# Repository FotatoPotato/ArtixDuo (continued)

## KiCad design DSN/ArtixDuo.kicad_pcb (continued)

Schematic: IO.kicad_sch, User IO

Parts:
C38, C39, C40, C41, C51, C52, C54, C166, C167, C168, C169, C170: 100nF; C_0402_1005Metric; MFR PN GRM155R71E104KE14J
C53, C163, C164, C165, C171, C172, C187, C188, C189, C190: 100nF; C_0402_1005Metric; MFR PN GRM155R71H104ME14J
C177, C197: 1nF; C_0402_1005Metric
C178, C179, C185, C186, C194, C196: 10uF; C_0805_2012Metric; MFR PN GRM21BC71E106KE01K
D12, D13, D14, D15, D16, D17, D18, D19, D20, D21, D22, D23, D24, D25, D26, D27: LED GREEN; LED_0603_1608Metric; MFR PN 150060VS75000
F1, F2: Fuse; Fuse_0603_1608Metric
J6, J8, J9: Conn_02x40_Top_Bottom; PinSocket_2x40_P2.54mm_Vertical
J7, J10: 47272-0001; MOLEX_47272-0001; MFR PN 47272-0001
J11, J12, J13, J14, J15, J16, J17, J18, J19: 5-1814832-1; RF_SMA_Vertical_5-1814832-1; MPN 5-1814832-1; Digi-Key_PN A97594-ND
J20, J21, J22, J23, J24, J25, J26, J33: Conn_02x06_Odd_Even; PinHeader_2x06_P2.54mm_Horizontal
Q5, Q6, Q7, Q8, Q9, Q10, Q11, Q12, Q13, Q14, Q15, Q16, Q17, Q18, Q19, Q20: 2N7002; SOT-23-3; MPN 2N7002; Digi-Key_PN 2N7002NCT-ND
R26, R27, R72, R73, R78, R79, R80, R104: 1Meg; R_0402_1005Metric
R28, R69, R71, R81: 100K; R_0402_1005Metric; MFR PN RT0402FRE07100KL
R65, R66, R67, R68, R88, R89, R90, R91, R111, R112, R113, R114, R115, R116, R117, R118, R124, R125, R126, R127, R128, R129, R130, R131, R136, R137, R138, R139, R140, R141, R142, R143, R144, R145, R146, R147, R148, R149, R150, R151: 3K3; R_0402_1005Metric; MFR PN RC0402FR-073K3L
R70: 1K; R_0402_1005Metric
R74, R75, R76, R77, R96, R97, R98, R99: 100K; R_0402_1005Metric; MFR PN RC0402FR-07100KL
R82, R119, R120, R121, R122, R123, R132, R133, R134, R135, R212, R213, R214, R215, R216, R226, R227, R228, R229: 0R; R_0402_1005Metric
R207, R208, R209, R210, R211, R217, R218, R219, R220, R221, R222, R223, R224, R225, R230, R231, R232, R233: DNF; R_0402_1005Metric
SW10, SW11, SW12, SW13, SW18, SW19, SW20, SW21: SW_Push; SW_SPST_EVQQ2

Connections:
+3V3: C178.1, C185.1, C194.1, F1.2, F2.2, J6.1, J6.2, J6.41, J6.42, J8.1, J8.2, J8.41, J8.42, J9.1, J9.2, J9.41, J9.42, J20.1, J20.2, J21.1, J21.2, J22.1, J22.2, J23.1, J23.2, J24.1, J24.2, J25.1, J25.2, J26.1, J26.2, J33.1, J33.2, R28.1, R65.1, R66.1, R67.1, R68.1, R79.2, R88.1, R89.1, R90.1, R91.1, R113.1, R114.1, R117.1, R118.1, R126.1, R127.1, R130.1, R131.1, R138.1, R139.1, R142.1, R143.1, R146.1, R147.1, R150.1, R151.1; also elsewhere on the board
/TopSheet/FPGA_0/FPGA_0_GTP_CLK1_N: R216.2, R221.1; also elsewhere on the board
/TopSheet/FPGA_0/FPGA_0_GTP_CLK1_P: R123.2, R221.2; also elsewhere on the board
/TopSheet/FPGA_0/FPGA_0_LED0: Q13.1 (G), R136.1; also elsewhere on the board
/TopSheet/FPGA_0/FPGA_0_LED1: Q15.1 (G), R140.1; also elsewhere on the board
/TopSheet/FPGA_0/FPGA_0_LED2: Q17.1 (G), R144.1; also elsewhere on the board
/TopSheet/FPGA_0/FPGA_0_LED3: Q19.1 (G), R148.1; also elsewhere on the board
/TopSheet/FPGA_0/FPGA_0_LED4: Q14.1 (G), R137.1; also elsewhere on the board
/TopSheet/FPGA_0/FPGA_0_LED5: Q16.1 (G), R141.1; also elsewhere on the board
/TopSheet/FPGA_0/FPGA_0_LED6: Q18.1 (G), R145.1; also elsewhere on the board
/TopSheet/FPGA_0/FPGA_0_LED7: Q20.1 (G), R149.1; also elsewhere on the board
/TopSheet/FPGA_0/FPGA_0_PMOD0_IO0: J24.12; also elsewhere on the board
/TopSheet/FPGA_0/FPGA_0_PMOD0_IO1: J24.10; also elsewhere on the board
/TopSheet/FPGA_0/FPGA_0_PMOD0_IO2: J24.8; also elsewhere on the board
/TopSheet/FPGA_0/FPGA_0_PMOD0_IO3: J24.6; also elsewhere on the board
/TopSheet/FPGA_0/FPGA_0_PMOD0_IO4: J24.11; also elsewhere on the board
/TopSheet/FPGA_0/FPGA_0_PMOD0_IO5: J24.9; also elsewhere on the board
/TopSheet/FPGA_0/FPGA_0_PMOD0_IO6: J24.7; also elsewhere on the board
/TopSheet/FPGA_0/FPGA_0_PMOD0_IO7: J24.5; also elsewhere on the board
/TopSheet/FPGA_0/FPGA_0_PMOD1_IO0: J25.12; also elsewhere on the board
/TopSheet/FPGA_0/FPGA_0_PMOD1_IO1: J25.10; also elsewhere on the board
/TopSheet/FPGA_0/FPGA_0_PMOD1_IO2: J25.8; also elsewhere on the board
/TopSheet/FPGA_0/FPGA_0_PMOD1_IO3: J25.6; also elsewhere on the board
/TopSheet/FPGA_0/FPGA_0_PMOD1_IO4: J25.11; also elsewhere on the board
/TopSheet/FPGA_0/FPGA_0_PMOD1_IO5: J25.9; also elsewhere on the board
/TopSheet/FPGA_0/FPGA_0_PMOD1_IO6: J25.7; also elsewhere on the board
/TopSheet/FPGA_0/FPGA_0_PMOD1_IO7: J25.5; also elsewhere on the board
/TopSheet/FPGA_0/FPGA_0_PMOD2_IO0: J33.12; also elsewhere on the board
/TopSheet/FPGA_0/FPGA_0_PMOD2_IO1: J33.10; also elsewhere on the board
/TopSheet/FPGA_0/FPGA_0_PMOD2_IO2: J33.8; also elsewhere on the board
/TopSheet/FPGA_0/FPGA_0_PMOD2_IO3: J33.6; also elsewhere on the board
/TopSheet/FPGA_0/FPGA_0_PMOD2_IO4: J33.11; also elsewhere on the board
/TopSheet/FPGA_0/FPGA_0_PMOD2_IO5: J33.9; also elsewhere on the board
/TopSheet/FPGA_0/FPGA_0_PMOD2_IO6: J33.7; also elsewhere on the board
/TopSheet/FPGA_0/FPGA_0_PMOD2_IO7: J33.5; also elsewhere on the board
/TopSheet/FPGA_0/FPGA_0_PMOD3_IO0: J26.12; also elsewhere on the board
/TopSheet/FPGA_0/FPGA_0_PMOD3_IO1: J26.10; also elsewhere on the board
/TopSheet/FPGA_0/FPGA_0_PMOD3_IO2: J26.8; also elsewhere on the board
/TopSheet/FPGA_0/FPGA_0_PMOD3_IO3: J26.6; also elsewhere on the board
/TopSheet/FPGA_0/FPGA_0_PMOD3_IO4: J26.11; also elsewhere on the board
/TopSheet/FPGA_0/FPGA_0_PMOD3_IO5: J26.9; also elsewhere on the board
/TopSheet/FPGA_0/FPGA_0_PMOD3_IO6: J26.7; also elsewhere on the board
/TopSheet/FPGA_0/FPGA_0_PMOD3_IO7: J26.5; also elsewhere on the board
/TopSheet/FPGA_0/FPGA_0_RXL0_N: R226.2, R230.1; also elsewhere on the board
/TopSheet/FPGA_0/FPGA_0_RXL0_P: R132.2, R230.2; also elsewhere on the board
/TopSheet/FPGA_0/FPGA_0_RXL1_N: R227.2, R231.1; also elsewhere on the board
/TopSheet/FPGA_0/FPGA_0_RXL1_P: R133.2, R231.2; also elsewhere on the board
/TopSheet/FPGA_0/FPGA_0_RXL2_N: R228.2, R232.1; also elsewhere on the board
/TopSheet/FPGA_0/FPGA_0_RXL2_P: R134.2, R232.2; also elsewhere on the board
/TopSheet/FPGA_0/FPGA_0_RXL3_N: R229.2, R233.1; also elsewhere on the board
/TopSheet/FPGA_0/FPGA_0_RXL3_P: R135.2, R233.2; also elsewhere on the board
/TopSheet/FPGA_0/FPGA_0_SW0: R74.2; also elsewhere on the board
/TopSheet/FPGA_0/FPGA_0_SW1: R75.2; also elsewhere on the board
/TopSheet/FPGA_0/FPGA_0_SW2: R76.2; also elsewhere on the board
/TopSheet/FPGA_0/FPGA_0_SW3: R77.2; also elsewhere on the board
/TopSheet/FPGA_0/FPGA_0_TXL0_N: R212.2, R217.1; also elsewhere on the board
/TopSheet/FPGA_0/FPGA_0_TXL0_P: R119.2, R217.2; also elsewhere on the board
/TopSheet/FPGA_0/FPGA_0_TXL1_N: R213.2, R218.1; also elsewhere on the board
/TopSheet/FPGA_0/FPGA_0_TXL1_P: R120.2, R218.2; also elsewhere on the board
/TopSheet/FPGA_0/FPGA_0_TXL2_N: R214.2, R219.1; also elsewhere on the board
/TopSheet/FPGA_0/FPGA_0_TXL2_P: R121.2, R219.2; also elsewhere on the board
/TopSheet/FPGA_0/FPGA_0_TXL3_N: R215.2, R220.1; also elsewhere on the board
/TopSheet/FPGA_0/FPGA_0_TXL3_P: R122.2, R220.2; also elsewhere on the board
/TopSheet/FPGA_0/FPGA_0_USER_IO0: J8.33; also elsewhere on the board
/TopSheet/FPGA_0/FPGA_0_USER_IO1: J8.46; also elsewhere on the board
/TopSheet/FPGA_0/FPGA_0_USER_IO2: J8.35; also elsewhere on the board
/TopSheet/FPGA_0/FPGA_0_USER_IO3: J8.48; also elsewhere on the board
/TopSheet/FPGA_0/FPGA_0_USER_IO4: J8.37; also elsewhere on the board
/TopSheet/FPGA_0/FPGA_0_USER_IO5: J8.50; also elsewhere on the board
/TopSheet/FPGA_0/FPGA_0_USER_IO6: J8.39; also elsewhere on the board
/TopSheet/FPGA_0/FPGA_0_USER_IO7: J8.52; also elsewhere on the board
/TopSheet/FPGA_0/FPGA_0_USER_IO8: J9.5; also elsewhere on the board
/TopSheet/FPGA_0/FPGA_0_USER_IO9: J8.54; also elsewhere on the board
/TopSheet/FPGA_0/FPGA_0_USER_IO10: J9.7; also elsewhere on the board
/TopSheet/FPGA_0/FPGA_0_USER_IO11: J8.56; also elsewhere on the board
/TopSheet/FPGA_0/FPGA_0_USER_IO12: J9.9; also elsewhere on the board
/TopSheet/FPGA_0/FPGA_0_USER_IO13: J8.58; also elsewhere on the board
/TopSheet/FPGA_0/FPGA_0_USER_IO14: J9.11; also elsewhere on the board
/TopSheet/FPGA_0/FPGA_0_USER_IO15: J8.60; also elsewhere on the board
/TopSheet/FPGA_0/FPGA_0_USER_IO16: J9.13; also elsewhere on the board
/TopSheet/FPGA_0/FPGA_0_USER_IO17: J8.62; also elsewhere on the board
/TopSheet/FPGA_0/FPGA_0_USER_IO18: J9.15; also elsewhere on the board
/TopSheet/FPGA_0/FPGA_0_USER_IO19: J8.64; also elsewhere on the board
/TopSheet/FPGA_0/FPGA_0_USER_IO20: J9.17; also elsewhere on the board
/TopSheet/FPGA_0/FPGA_0_USER_IO21: J8.66; also elsewhere on the board
/TopSheet/FPGA_0/FPGA_0_USER_IO22: J9.19; also elsewhere on the board
/TopSheet/FPGA_0/FPGA_0_USER_IO23: J8.68; also elsewhere on the board
/TopSheet/FPGA_0/FPGA_0_USER_IO24: J9.21; also elsewhere on the board
/TopSheet/FPGA_0/FPGA_0_USER_IO25: J8.70; also elsewhere on the board
/TopSheet/FPGA_0/FPGA_0_USER_IO26: J9.23; also elsewhere on the board
/TopSheet/FPGA_0/FPGA_0_USER_IO27: J8.72; also elsewhere on the board
/TopSheet/FPGA_0/FPGA_0_USER_IO28: J9.25; also elsewhere on the board
/TopSheet/FPGA_0/FPGA_0_USER_IO29: J8.74; also elsewhere on the board
/TopSheet/FPGA_0/FPGA_0_USER_IO30: J9.27; also elsewhere on the board
/TopSheet/FPGA_0/FPGA_0_USER_IO31: J8.76; also elsewhere on the board
/TopSheet/FPGA_0/FPGA_0_USER_IO32: J9.29; also elsewhere on the board
/TopSheet/FPGA_0/FPGA_0_USER_IO33: J8.78; also elsewhere on the board
/TopSheet/FPGA_0/FPGA_0_USER_IO34: J9.31; also elsewhere on the board
/TopSheet/FPGA_0/FPGA_0_USER_IO35: J8.80; also elsewhere on the board
/TopSheet/FPGA_0/FPGA_0_USER_IO36: J9.33; also elsewhere on the board
/TopSheet/FPGA_0/FPGA_0_USER_IO37: J9.46; also elsewhere on the board
/TopSheet/FPGA_0/FPGA_0_USER_IO38: J9.35; also elsewhere on the board
/TopSheet/FPGA_0/FPGA_0_USER_IO39: J9.48; also elsewhere on the board
/TopSheet/FPGA_0/FPGA_0_USER_IO40: J9.37; also elsewhere on the board
/TopSheet/FPGA_0/FPGA_0_USER_IO41: J9.50; also elsewhere on the board
/TopSheet/FPGA_0/FPGA_0_USER_IO42: J9.39; also elsewhere on the board
/TopSheet/FPGA_0/FPGA_0_USER_IO43: J9.52; also elsewhere on the board
/TopSheet/FPGA_0/FPGA_0_USER_IO44: J9.60; also elsewhere on the board
/TopSheet/FPGA_0/FPGA_0_USER_IO45: J9.54; also elsewhere on the board
/TopSheet/FPGA_0/FPGA_0_USER_IO46: J9.62; also elsewhere on the board
/TopSheet/FPGA_0/FPGA_0_USER_IO47: J9.56; also elsewhere on the board
/TopSheet/FPGA_0/FPGA_0_USER_IO48: J9.64; also elsewhere on the board
/TopSheet/FPGA_0/FPGA_0_USER_IO49: J9.58; also elsewhere on the board
/TopSheet/FPGA_1/FPGA_1_DP_RXL0_N: J10.10; also elsewhere on the board
/TopSheet/FPGA_1/FPGA_1_DP_RXL0_P: J10.12; also elsewhere on the board
/TopSheet/FPGA_1/FPGA_1_DP_RXL1_N: J10.7; also elsewhere on the board
/TopSheet/FPGA_1/FPGA_1_DP_RXL1_P: J10.9; also elsewhere on the board
/TopSheet/FPGA_1/FPGA_1_DP_RXL2_N: J10.4; also elsewhere on the board
/TopSheet/FPGA_1/FPGA_1_DP_RXL2_P: J10.6; also elsewhere on the board
/TopSheet/FPGA_1/FPGA_1_DP_RXL3_N: J10.1; also elsewhere on the board
/TopSheet/FPGA_1/FPGA_1_DP_RXL3_P: C166.1; also elsewhere on the board
/TopSheet/FPGA_1/FPGA_1_DP_RX_AUX_N: C169.2; also elsewhere on the board
/TopSheet/FPGA_1/FPGA_1_DP_RX_AUX_P: C170.1; also elsewhere on the board
/TopSheet/FPGA_1/FPGA_1_DP_RX_HPD: R82.2; also elsewhere on the board
/TopSheet/FPGA_1/FPGA_1_DP_TXL0_N: C39.2; also elsewhere on the board
/TopSheet/FPGA_1/FPGA_1_DP_TXL0_P: C51.1; also elsewhere on the board
/TopSheet/FPGA_1/FPGA_1_DP_TXL1_N: C167.2; also elsewhere on the board
/TopSheet/FPGA_1/FPGA_1_DP_TXL1_P: C54.1; also elsewhere on the board
/TopSheet/FPGA_1/FPGA_1_DP_TXL2_N: C40.2; also elsewhere on the board
/TopSheet/FPGA_1/FPGA_1_DP_TXL2_P: C52.1; also elsewhere on the board
/TopSheet/FPGA_1/FPGA_1_DP_TXL3_N: C168.2; also elsewhere on the board
/TopSheet/FPGA_1/FPGA_1_DP_TXL3_P: J10.3; also elsewhere on the board
/TopSheet/FPGA_1/FPGA_1_DP_TX_AUX_N: C38.2; also elsewhere on the board
/TopSheet/FPGA_1/FPGA_1_DP_TX_AUX_P: C41.1; also elsewhere on the board
/TopSheet/FPGA_1/FPGA_1_DP_TX_HPD: R70.2; also elsewhere on the board
/TopSheet/FPGA_1/FPGA_1_LED0: Q5.1 (G), R111.1; also elsewhere on the board
/TopSheet/FPGA_1/FPGA_1_LED1: Q7.1 (G), R115.1; also elsewhere on the board
/TopSheet/FPGA_1/FPGA_1_LED2: Q9.1 (G), R124.1; also elsewhere on the board
/TopSheet/FPGA_1/FPGA_1_LED3: Q11.1 (G), R128.1; also elsewhere on the board
/TopSheet/FPGA_1/FPGA_1_LED4: Q6.1 (G), R112.1; also elsewhere on the board
/TopSheet/FPGA_1/FPGA_1_LED5: Q8.1 (G), R116.1; also elsewhere on the board
/TopSheet/FPGA_1/FPGA_1_LED6: Q10.1 (G), R125.1; also elsewhere on the board
/TopSheet/FPGA_1/FPGA_1_LED7: Q12.1 (G), R129.1; also elsewhere on the board
/TopSheet/FPGA_1/FPGA_1_PMOD0_IO0: J20.12; also elsewhere on the board
/TopSheet/FPGA_1/FPGA_1_PMOD0_IO1: J20.10; also elsewhere on the board
/TopSheet/FPGA_1/FPGA_1_PMOD0_IO2: J20.8; also elsewhere on the board
/TopSheet/FPGA_1/FPGA_1_PMOD0_IO3: J20.6; also elsewhere on the board
/TopSheet/FPGA_1/FPGA_1_PMOD0_IO4: J20.11; also elsewhere on the board
/TopSheet/FPGA_1/FPGA_1_PMOD0_IO5: J20.9; also elsewhere on the board
/TopSheet/FPGA_1/FPGA_1_PMOD0_IO6: J20.7; also elsewhere on the board
/TopSheet/FPGA_1/FPGA_1_PMOD0_IO7: J20.5; also elsewhere on the board
/TopSheet/FPGA_1/FPGA_1_PMOD1_IO0: J21.12; also elsewhere on the board
/TopSheet/FPGA_1/FPGA_1_PMOD1_IO1: J21.10; also elsewhere on the board
/TopSheet/FPGA_1/FPGA_1_PMOD1_IO2: J21.8; also elsewhere on the board
/TopSheet/FPGA_1/FPGA_1_PMOD1_IO3: J21.6; also elsewhere on the board
/TopSheet/FPGA_1/FPGA_1_PMOD1_IO4: J21.11; also elsewhere on the board
/TopSheet/FPGA_1/FPGA_1_PMOD1_IO5: J21.9; also elsewhere on the board
/TopSheet/FPGA_1/FPGA_1_PMOD1_IO6: J21.7; also elsewhere on the board
/TopSheet/FPGA_1/FPGA_1_PMOD1_IO7: J21.5; also elsewhere on the board
/TopSheet/FPGA_1/FPGA_1_PMOD2_IO0: J22.12; also elsewhere on the board
/TopSheet/FPGA_1/FPGA_1_PMOD2_IO1: J22.10; also elsewhere on the board
/TopSheet/FPGA_1/FPGA_1_PMOD2_IO2: J22.8; also elsewhere on the board
/TopSheet/FPGA_1/FPGA_1_PMOD2_IO3: J22.6; also elsewhere on the board
/TopSheet/FPGA_1/FPGA_1_PMOD2_IO4: J22.11; also elsewhere on the board
/TopSheet/FPGA_1/FPGA_1_PMOD2_IO5: J22.9; also elsewhere on the board
/TopSheet/FPGA_1/FPGA_1_PMOD2_IO6: J22.7; also elsewhere on the board
/TopSheet/FPGA_1/FPGA_1_PMOD2_IO7: J22.5; also elsewhere on the board
/TopSheet/FPGA_1/FPGA_1_PMOD3_IO0: J23.12; also elsewhere on the board
/TopSheet/FPGA_1/FPGA_1_PMOD3_IO1: J23.10; also elsewhere on the board
/TopSheet/FPGA_1/FPGA_1_PMOD3_IO2: J23.8; also elsewhere on the board
/TopSheet/FPGA_1/FPGA_1_PMOD3_IO3: J23.6; also elsewhere on the board
/TopSheet/FPGA_1/FPGA_1_PMOD3_IO4: J23.11; also elsewhere on the board
/TopSheet/FPGA_1/FPGA_1_PMOD3_IO5: J23.9; also elsewhere on the board
/TopSheet/FPGA_1/FPGA_1_PMOD3_IO6: J23.7; also elsewhere on the board
/TopSheet/FPGA_1/FPGA_1_PMOD3_IO7: J23.5; also elsewhere on the board
/TopSheet/FPGA_1/FPGA_1_SW0: R96.2; also elsewhere on the board
/TopSheet/FPGA_1/FPGA_1_SW1: R97.2; also elsewhere on the board
/TopSheet/FPGA_1/FPGA_1_SW2: R98.2; also elsewhere on the board
/TopSheet/FPGA_1/FPGA_1_SW3: R99.2; also elsewhere on the board
/TopSheet/FPGA_1/FPGA_1_USER_IO0: J6.5; also elsewhere on the board
/TopSheet/FPGA_1/FPGA_1_USER_IO1: J6.46; also elsewhere on the board
/TopSheet/FPGA_1/FPGA_1_USER_IO2: J6.7; also elsewhere on the board
/TopSheet/FPGA_1/FPGA_1_USER_IO3: J6.48; also elsewhere on the board
/TopSheet/FPGA_1/FPGA_1_USER_IO4: J6.9; also elsewhere on the board
/TopSheet/FPGA_1/FPGA_1_USER_IO5: J6.50; also elsewhere on the board
/TopSheet/FPGA_1/FPGA_1_USER_IO6: J6.11; also elsewhere on the board
/TopSheet/FPGA_1/FPGA_1_USER_IO7: J6.52; also elsewhere on the board
/TopSheet/FPGA_1/FPGA_1_USER_IO8: J6.13; also elsewhere on the board
/TopSheet/FPGA_1/FPGA_1_USER_IO9: J6.54; also elsewhere on the board
/TopSheet/FPGA_1/FPGA_1_USER_IO10: J6.15; also elsewhere on the board
/TopSheet/FPGA_1/FPGA_1_USER_IO11: J6.56; also elsewhere on the board
/TopSheet/FPGA_1/FPGA_1_USER_IO12: J6.17; also elsewhere on the board
/TopSheet/FPGA_1/FPGA_1_USER_IO13: J6.58; also elsewhere on the board
/TopSheet/FPGA_1/FPGA_1_USER_IO14: J6.19; also elsewhere on the board
/TopSheet/FPGA_1/FPGA_1_USER_IO15: J6.60; also elsewhere on the board
/TopSheet/FPGA_1/FPGA_1_USER_IO16: J6.21; also elsewhere on the board
/TopSheet/FPGA_1/FPGA_1_USER_IO17: J6.62; also elsewhere on the board
/TopSheet/FPGA_1/FPGA_1_USER_IO18: J6.23; also elsewhere on the board
/TopSheet/FPGA_1/FPGA_1_USER_IO19: J6.64; also elsewhere on the board
/TopSheet/FPGA_1/FPGA_1_USER_IO20: J6.25; also elsewhere on the board
/TopSheet/FPGA_1/FPGA_1_USER_IO21: J6.66; also elsewhere on the board
/TopSheet/FPGA_1/FPGA_1_USER_IO22: J6.27; also elsewhere on the board
/TopSheet/FPGA_1/FPGA_1_USER_IO23: J6.68; also elsewhere on the board
/TopSheet/FPGA_1/FPGA_1_USER_IO24: J6.29; also elsewhere on the board
/TopSheet/FPGA_1/FPGA_1_USER_IO25: J6.70; also elsewhere on the board
/TopSheet/FPGA_1/FPGA_1_USER_IO26: J6.31; also elsewhere on the board
/TopSheet/FPGA_1/FPGA_1_USER_IO27: J6.72; also elsewhere on the board
/TopSheet/FPGA_1/FPGA_1_USER_IO28: J6.33; also elsewhere on the board
/TopSheet/FPGA_1/FPGA_1_USER_IO29: J6.74; also elsewhere on the board
/TopSheet/FPGA_1/FPGA_1_USER_IO30: J6.35; also elsewhere on the board
/TopSheet/FPGA_1/FPGA_1_USER_IO31: J6.76; also elsewhere on the board
/TopSheet/FPGA_1/FPGA_1_USER_IO32: J6.37; also elsewhere on the board
/TopSheet/FPGA_1/FPGA_1_USER_IO33: J6.78; also elsewhere on the board
/TopSheet/FPGA_1/FPGA_1_USER_IO34: J6.39; also elsewhere on the board
/TopSheet/FPGA_1/FPGA_1_USER_IO35: J6.80; also elsewhere on the board
/TopSheet/FPGA_1/FPGA_1_USER_IO36: J8.19; also elsewhere on the board
/TopSheet/FPGA_1/FPGA_1_USER_IO37: J8.5; also elsewhere on the board
/TopSheet/FPGA_1/FPGA_1_USER_IO38: J8.21; also elsewhere on the board
/TopSheet/FPGA_1/FPGA_1_USER_IO39: J8.7; also elsewhere on the board
/TopSheet/FPGA_1/FPGA_1_USER_IO40: J8.23; also elsewhere on the board
/TopSheet/FPGA_1/FPGA_1_USER_IO41: J8.9; also elsewhere on the board
/TopSheet/FPGA_1/FPGA_1_USER_IO42: J8.25; also elsewhere on the board
/TopSheet/FPGA_1/FPGA_1_USER_IO43: J8.11; also elsewhere on the board
/TopSheet/FPGA_1/FPGA_1_USER_IO44: J8.27; also elsewhere on the board
/TopSheet/FPGA_1/FPGA_1_USER_IO45: J8.13; also elsewhere on the board
/TopSheet/FPGA_1/FPGA_1_USER_IO46: J8.29; also elsewhere on the board
/TopSheet/FPGA_1/FPGA_1_USER_IO47: J8.15; also elsewhere on the board
/TopSheet/FPGA_1/FPGA_1_USER_IO48: J8.31; also elsewhere on the board
/TopSheet/FPGA_1/FPGA_1_USER_IO49: J8.17; also elsewhere on the board
/TopSheet/UserIO/DP_RX_CFG1: J10.13, R73.2
/TopSheet/UserIO/DP_RX_CFG2: J10.14, R78.2
/TopSheet/UserIO/DP_RX_C_AUX_N: C169.1, J10.17, R79.1
/TopSheet/UserIO/DP_RX_C_AUX_P: C170.2, J10.15, R80.1
/TopSheet/UserIO/DP_RX_PWR: C171.1, F2.1, J10.20
/TopSheet/UserIO/DP_TX_CFG1: J7.13, R26.2
/TopSheet/UserIO/DP_TX_CFG2: J7.14, R27.2
/TopSheet/UserIO/DP_TX_C_AUX_N: C38.1, J7.17, R28.2
/TopSheet/UserIO/DP_TX_C_AUX_P: C41.2, J7.15, R69.2
/TopSheet/UserIO/DP_TX_C_LANE0_N: C39.1, J7.3
/TopSheet/UserIO/DP_TX_C_LANE0_P: C51.2, J7.1
/TopSheet/UserIO/DP_TX_C_LANE1_N: C167.1, J7.6
/TopSheet/UserIO/DP_TX_C_LANE1_P: C54.2, J7.4
/TopSheet/UserIO/DP_TX_C_LANE2_N: C40.1, J7.9
/TopSheet/UserIO/DP_TX_C_LANE2_P: C52.2, J7.7
/TopSheet/UserIO/DP_TX_C_LANE3_N: C168.1, J7.12
/TopSheet/UserIO/DP_TX_C_LANE3_P: C166.2, J7.10
/TopSheet/UserIO/DP_TX_PWR: C53.1, F1.1, J7.20
/TopSheet/UserIO/FPGA_0_RC_CLK1_N: J15.1, R211.1, R216.1
/TopSheet/UserIO/FPGA_0_RC_CLK1_P: J15.2, R123.1, R211.2
/TopSheet/UserIO/FPGA_0_RC_RX0_N: J16.1, R222.1, R226.1
/TopSheet/UserIO/FPGA_0_RC_RX0_P: J16.2, R132.1, R222.2
/TopSheet/UserIO/FPGA_0_RC_RX1_N: J17.1, R223.1, R227.1
/TopSheet/UserIO/FPGA_0_RC_RX1_P: J17.2, R133.1, R223.2
/TopSheet/UserIO/FPGA_0_RC_RX2_N: J18.1, R224.1, R228.1
/TopSheet/UserIO/FPGA_0_RC_RX2_P: J18.2, R134.1, R224.2
/TopSheet/UserIO/FPGA_0_RC_RX3_N: J19.1, R225.1, R229.1
/TopSheet/UserIO/FPGA_0_RC_RX3_P: J19.2, R135.1, R225.2
/TopSheet/UserIO/FPGA_0_RC_TX0_N: J11.1, R207.1, R212.1
/TopSheet/UserIO/FPGA_0_RC_TX0_P: J11.2, R119.1, R207.2
/TopSheet/UserIO/FPGA_0_RC_TX1_N: J12.1, R208.1, R213.1
/TopSheet/UserIO/FPGA_0_RC_TX1_P: J12.2, R120.1, R208.2
/TopSheet/UserIO/FPGA_0_RC_TX2_N: J13.1, R209.1, R214.1
/TopSheet/UserIO/FPGA_0_RC_TX2_P: J13.2, R121.1, R209.2
/TopSheet/UserIO/FPGA_0_RC_TX3_N: J14.1, R210.1, R215.1
/TopSheet/UserIO/FPGA_0_RC_TX3_P: J14.2, R122.1, R210.2
/TopSheet/UserIO/FPGA_0_SW0_R: C187.1, R88.2, R96.1, SW18.2
/TopSheet/UserIO/FPGA_0_SW1_R: C188.1, R89.2, R97.1, SW19.2
/TopSheet/UserIO/FPGA_0_SW2_R: C189.1, R90.2, R98.1, SW20.2
/TopSheet/UserIO/FPGA_0_SW3_R: C190.1, R91.2, R99.1, SW21.2
/TopSheet/UserIO/FPGA_1_SW0_R: C163.1, R65.2, R74.1, SW10.2
/TopSheet/UserIO/FPGA_1_SW1_R: C164.1, R66.2, R75.1, SW11.2
/TopSheet/UserIO/FPGA_1_SW2_R: C165.1, R67.2, R76.1, SW12.2
/TopSheet/UserIO/FPGA_1_SW3_R: C172.1, R68.2, R77.1, SW13.2
unnamed: C177.1, J7.SH, R72.1
unnamed: C197.1, J10.SH, R104.1
unnamed: D12.1 (K), Q5.3 (D)
unnamed: D12.2 (A), R113.2
unnamed: D13.1 (K), Q6.3 (D)
unnamed: D13.2 (A), R114.2
unnamed: D14.1 (K), Q7.3 (D)
unnamed: D14.2 (A), R117.2
unnamed: D15.1 (K), Q8.3 (D)
unnamed: D15.2 (A), R118.2
unnamed: D16.1 (K), Q9.3 (D)
unnamed: D16.2 (A), R126.2
unnamed: D17.1 (K), Q10.3 (D)
unnamed: D17.2 (A), R127.2
unnamed: D18.1 (K), Q11.3 (D)
unnamed: D18.2 (A), R130.2
unnamed: D19.1 (K), Q12.3 (D)
unnamed: D19.2 (A), R131.2
unnamed: D20.1 (K), Q13.3 (D)
unnamed: D20.2 (A), R138.2
unnamed: D21.1 (K), Q14.3 (D)
unnamed: D21.2 (A), R139.2
unnamed: D22.1 (K), Q15.3 (D)
unnamed: D22.2 (A), R142.2
unnamed: D23.1 (K), Q16.3 (D)
unnamed: D23.2 (A), R143.2
unnamed: D24.1 (K), Q17.3 (D)
unnamed: D24.2 (A), R146.2
unnamed: D25.1 (K), Q18.3 (D)
unnamed: D25.2 (A), R147.2
unnamed: D26.1 (K), Q19.3 (D)
unnamed: D26.2 (A), R150.2
unnamed: D27.1 (K), Q20.3 (D)
unnamed: D27.2 (A), R151.2

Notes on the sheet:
USER BUTTONS
High Density 3V3 User IO
USER PMOD
USER GTP (ONLY ON FPGA_0)
USER LED's
DP RX
USER DISPLAYPORT (ONLY ON FPGA_1)
DP TX

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
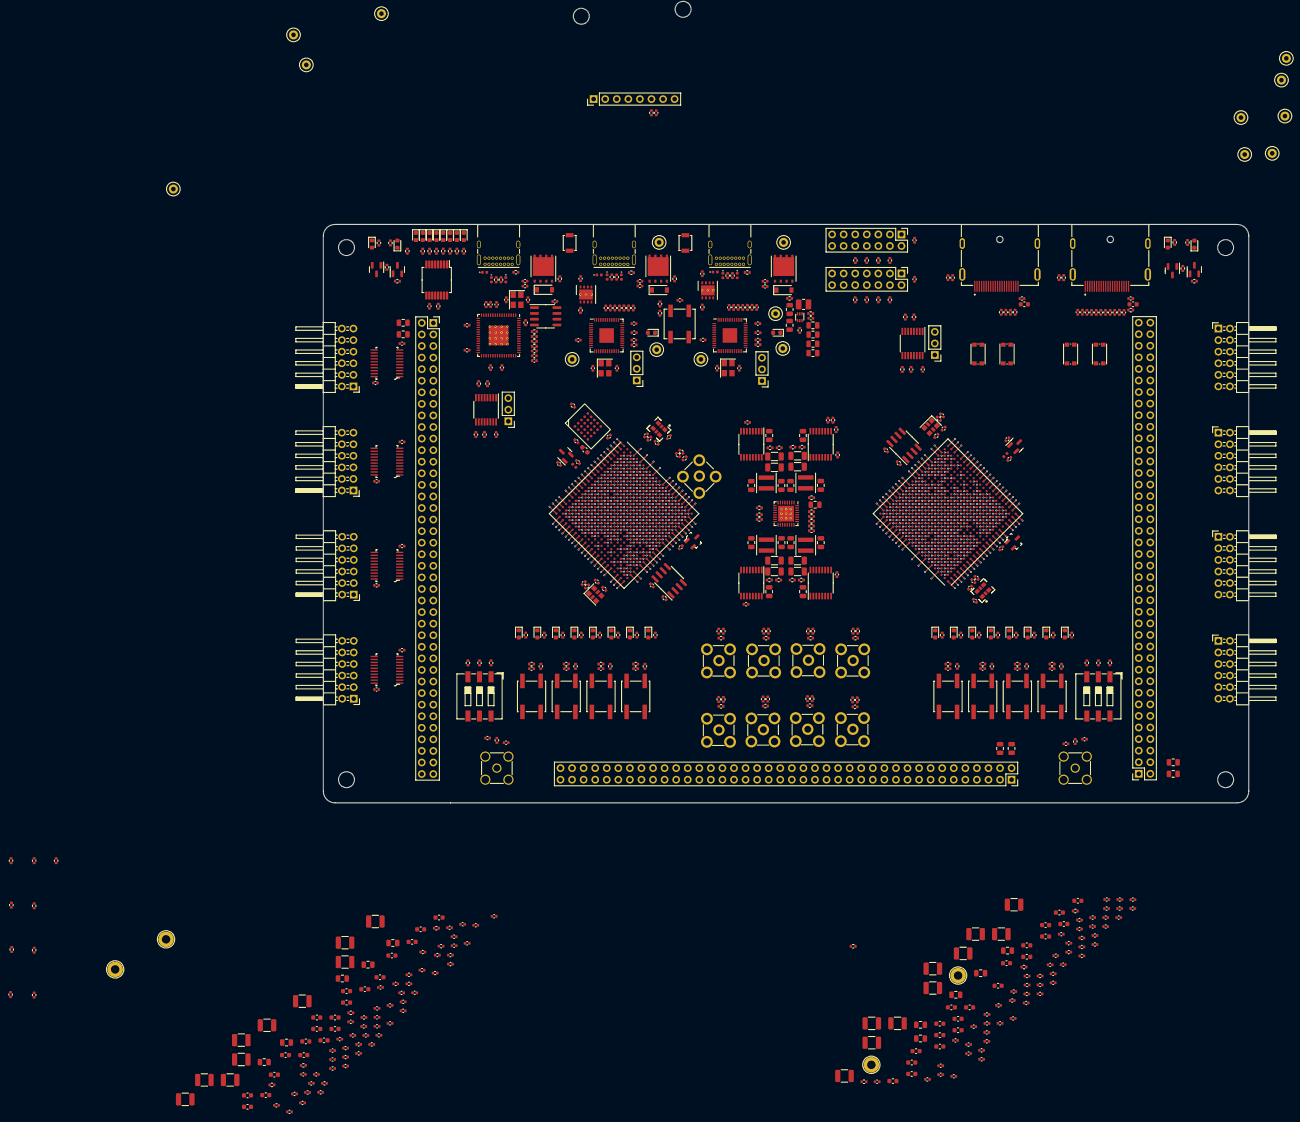
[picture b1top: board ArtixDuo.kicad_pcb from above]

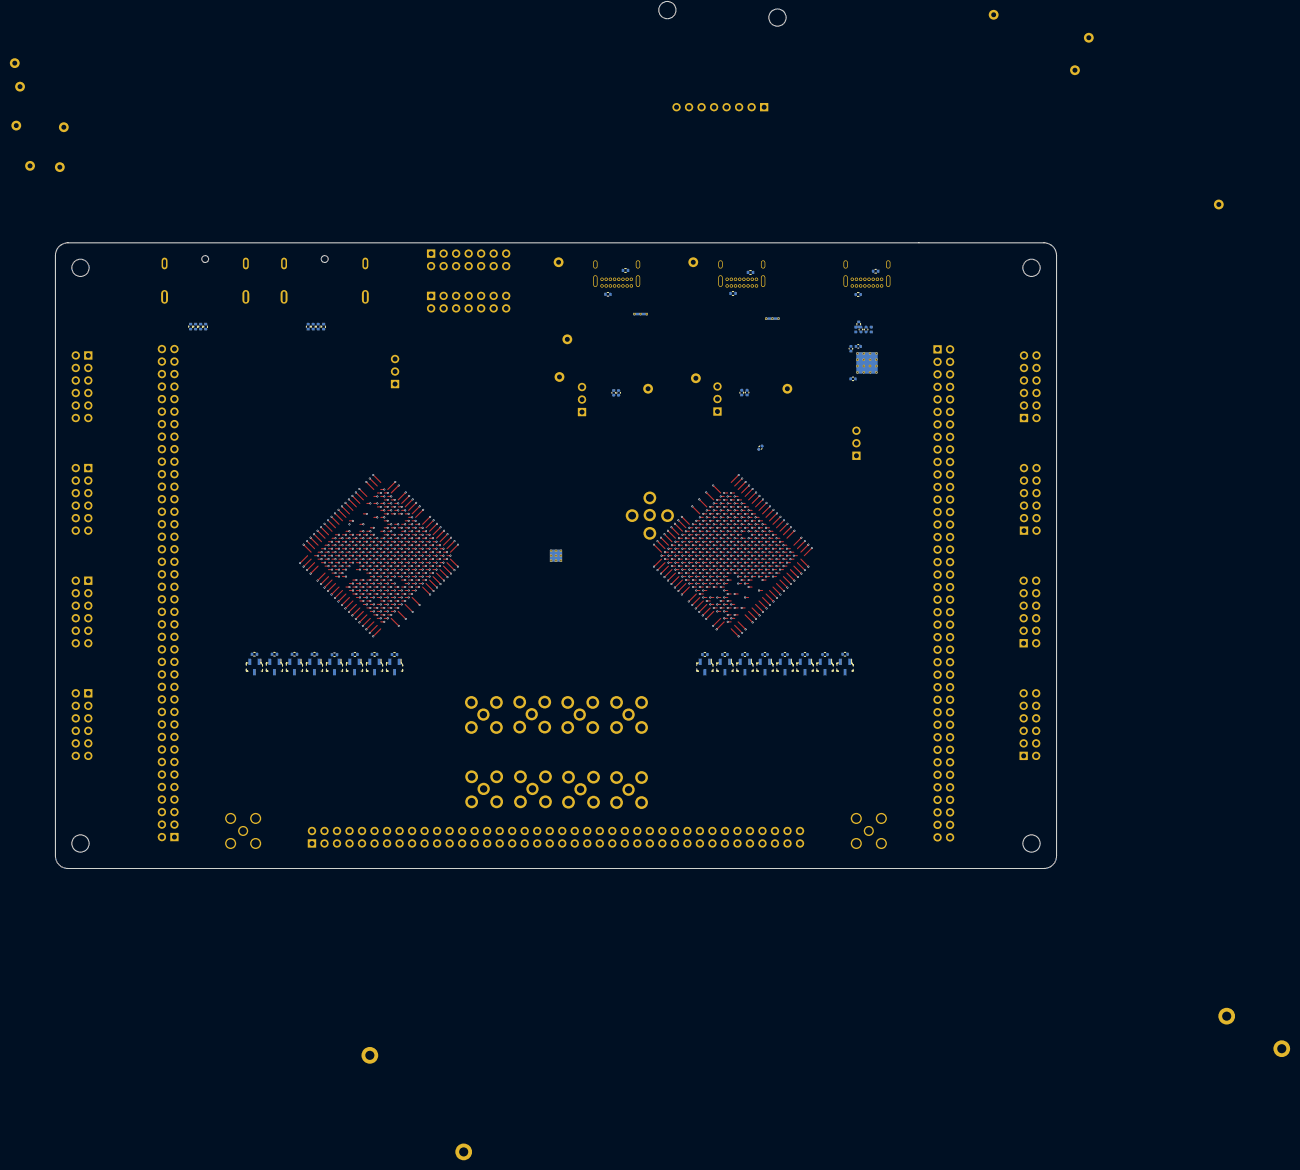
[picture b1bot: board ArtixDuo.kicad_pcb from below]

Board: 8 copper layers, 203.2 x 127.0 mm, 733 parts (59 on the bottom side), 701 nets.

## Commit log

2023-03-07 Updates
    Changed FPGA user io from 100 to 50 per chip, added 4 pmod per FPGA, added 8x buttons + led's, added SMA connectors for FPGA0 GTP.
2023-03-08 Added PSRAM, Finished Schematic
    Footprint assignment required, some minor changes to be made to schematic. Sheet naming and commenting to be done.
2023-03-08 Removed DDR Sheet
    Sheet is not needed
2023-03-08 Added Footprints
2023-03-08 Added component ref des
2023-03-11 Fixed all ERC Errors
    Warnings can be ignored
2023-03-11 Initial PCB Layout
    Initial layout and part placement
2023-03-11 Updated Layout
2023-03-12 Layout Update
